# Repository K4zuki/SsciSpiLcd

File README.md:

# idea

- breadboard-able breakout board for color SPI memory LCD from Switch Science
    - https://www.switch-science.com/catalog/2858/

# spec

26.02x27.82 mm<sup>2</sup> LCD
- 42x35mm pcb
    - 4~6 panelize
- AkiSpiLcd compatible and extention
    - 541 buffer + 3-state buffer + NAND
- 23K256 SRAM
    - persudo DMA
- 3.3V LDO
- 1x8 pin headers left and right
    - VDD = 5V
    - GND
    - SPI.SCK
    - SPI.MOSI
    - SPI.MISO
    - SPI.CSL
    - SPI.CSR
    - LCD.DISP

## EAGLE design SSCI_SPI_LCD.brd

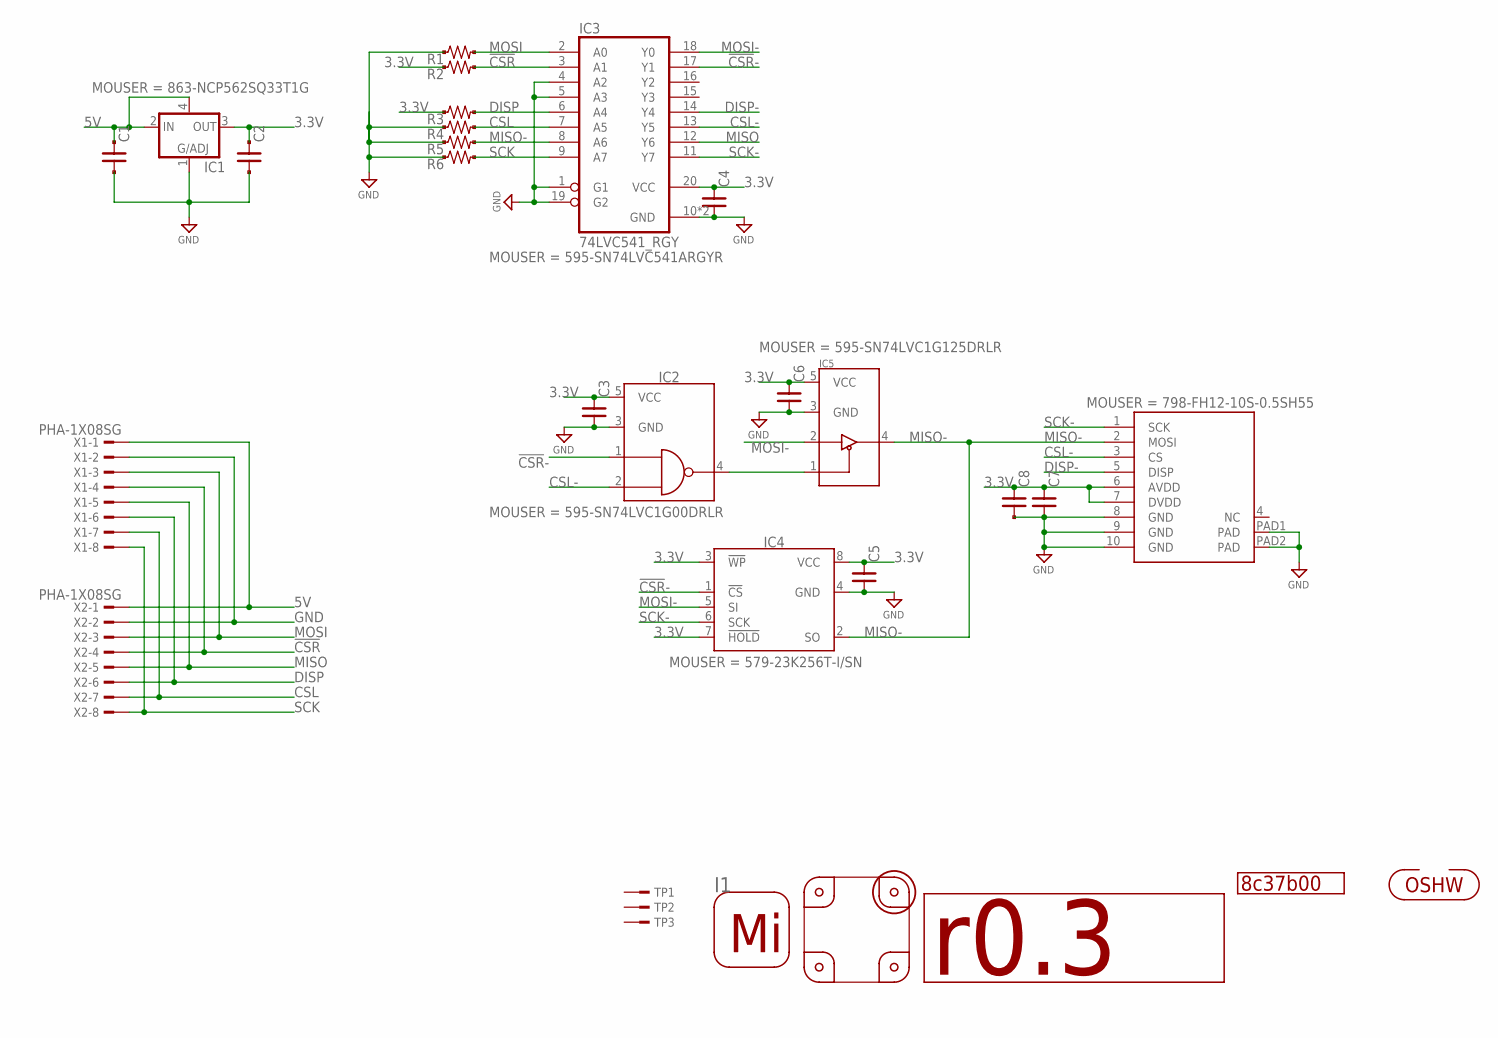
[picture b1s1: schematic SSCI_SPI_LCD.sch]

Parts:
C1, C2: C_SMD_10U_1608; CR_1608
C3, C4, C5, C6, C7, C8: C_SMD_0.1U_1005; C0402
GIT1: 8c37b00; GIT-REVISION_1.2
I1: ICON_MINLAB_5.2S; ICON_MINLAB_5.2MM
IC1: LDO4_3.3_SC82-AB; SOT130P220X135-4N
IC2: 74LVC1G00_DRL; SOT50P160X120-5N
IC3: 74LVC541_RGY; QFN50P460X360-20N
IC4: IC_MEMORY_8P_23K256-I_SOP; IC_08_1.27_150MIL
IC5: 74LVC1G125_DRL; SOT50P160X120-5N
ICON1: r0.3; ICON_REVISION1.7
ICON2: ICON_OSHW
LCD1: LCD_GLCD_400X240
P1, P2, P3, P4: PCB_CORNER_NH
R1, R2, R3, R4, R5, R6: R_US_10K_1005; C0402
TP1, TP2, TP3: TESTPAD_F; FIDUCIAL
X1, X2: PHA-1X08SG

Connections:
3.3V: C2.1, C3.1, C4.1, C5.1, C6.1, C7.1, C8.1, IC1.3 (OUT), IC2.5 (VCC), IC3.20 (VCC), IC4.3 (!WP), IC4.7 (!HOLD), IC4.8 (VCC), IC5.5 (VCC), LCD1.6 (AVDD), LCD1.7 (DVDD), R2.1, R3.1
5V: C1.1, IC1.2 (IN), IC1.4 (OUT/EN/NC), X1.1, X2.1
!CSR!: IC3.3 (A1), R2.2, X1.4, X2.4
!CSR!-: IC2.1 (1A), IC3.17 (Y1), IC4.1 (!CS)
CSL: IC3.7 (A5), R4.2, X1.7, X2.7
CSL-: IC2.2 (1B), IC3.13 (Y5), LCD1.3 (CS)
DISP: IC3.6 (A4), R3.2, X1.6, X2.6
DISP-: IC3.14 (Y4), LCD1.5 (DISP)
GND: C1.2, C2.2, C3.2, C4.2, C5.2, C6.2, C7.2, C8.2, IC1.1 (ADJ), IC2.3 (GND), IC3.1 (G1), IC3.4 (A2), IC3.5 (A3), IC3.10 (GND), IC3.19 (G2), IC3.EP (GND), IC4.4 (GND), IC5.3 (GND), LCD1.8 (GND), LCD1.9 (GND), LCD1.10 (GND), LCD1.PAD1 (PAD), LCD1.PAD2 (PAD), R1.1, R4.1, R5.1, R6.1, X1.2, X2.2
MISO: IC3.12 (Y6), X1.5, X2.5
MISO-: IC3.8 (A6), IC4.2 (SO), IC5.4 (Y), LCD1.2 (MOSI), R5.2
MOSI: IC3.2 (A0), R1.2, X1.3, X2.3
MOSI-: IC3.18 (Y0), IC4.5 (SI), IC5.2 (A)
unnamed: IC2.4 (1Y), IC5.1 (!OE!)
SCK: IC3.9 (A7), R6.2, X1.8, X2.8
SCK-: IC3.11 (Y7), IC4.6 (SCK), LCD1.1 (SCK)

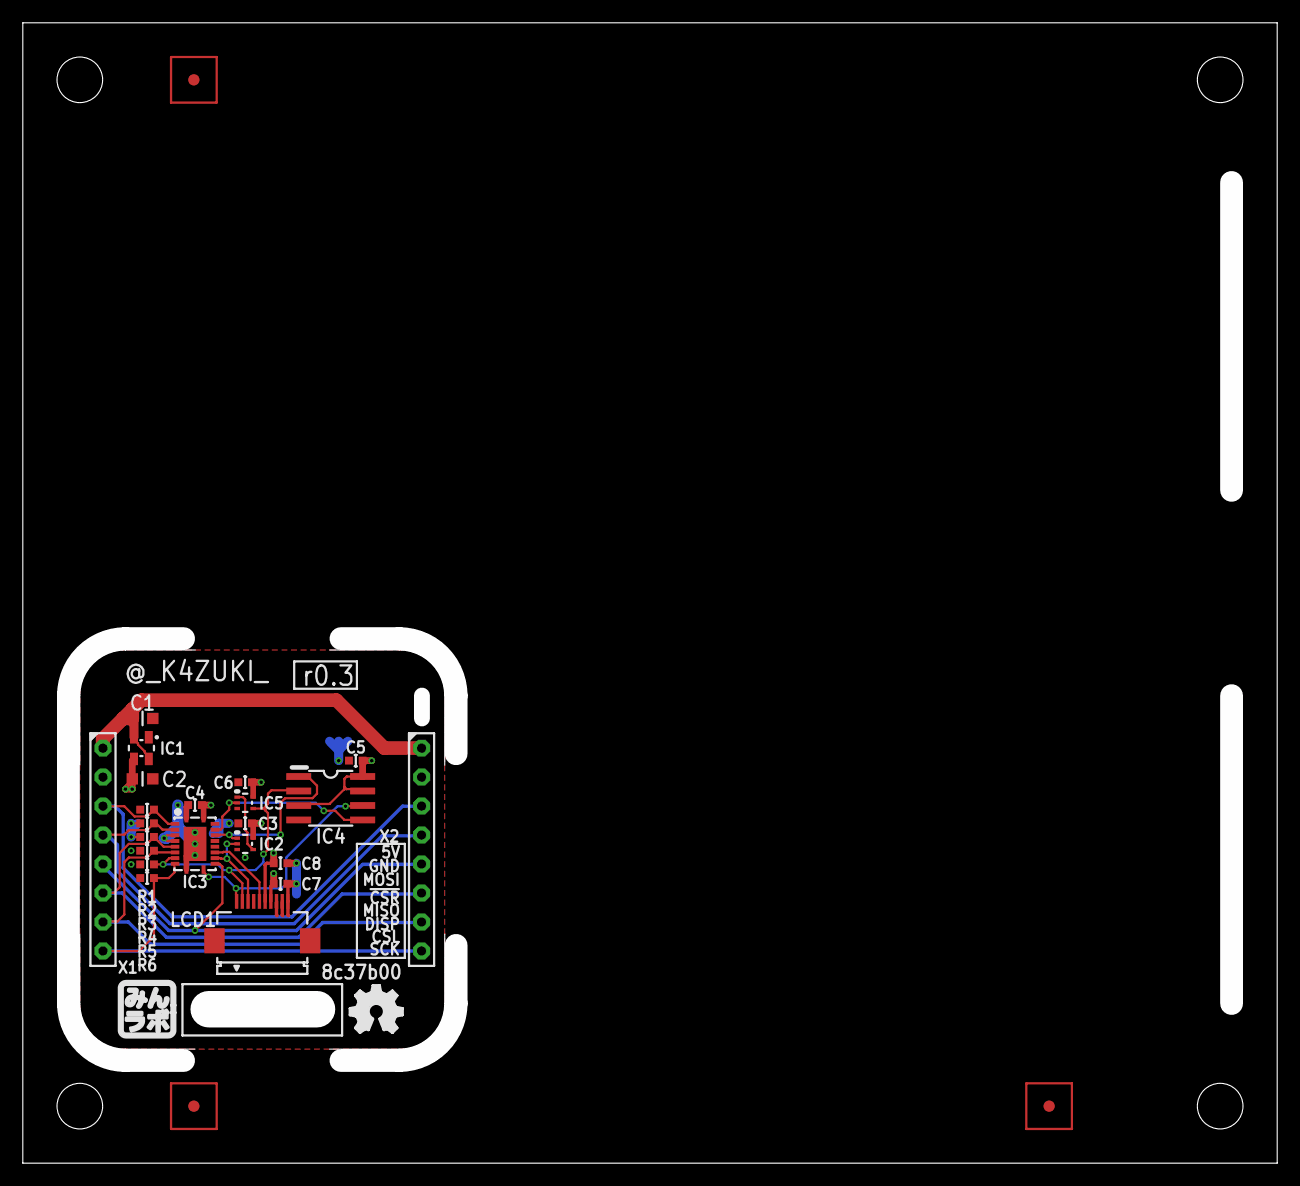
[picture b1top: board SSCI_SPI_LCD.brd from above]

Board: 2 copper layers, 106.8 x 96.8 mm, 33 parts (0 on the bottom side), 16 nets.

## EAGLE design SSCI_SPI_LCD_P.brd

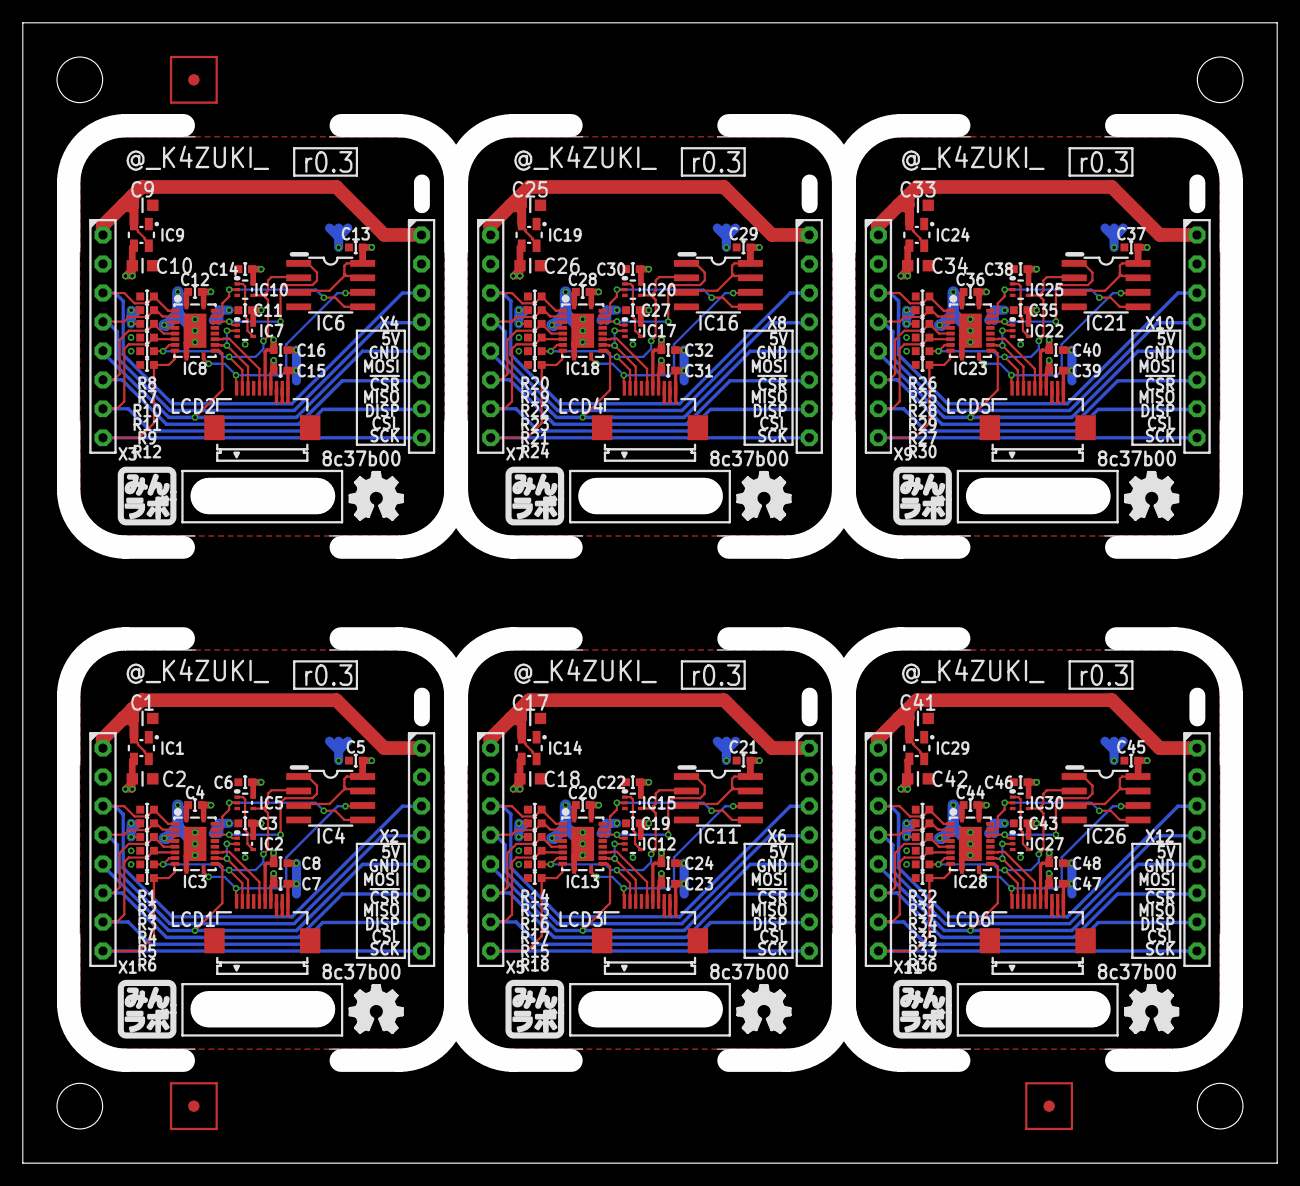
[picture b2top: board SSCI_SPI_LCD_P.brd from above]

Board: 2 copper layers, 106.8 x 96.8 mm, 183 parts (0 on the bottom side), 96 nets.

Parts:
C1, C2, C9, C10, C17, C18, C25, C26, C33, C34, C41, C42: CR_1608
C3, C4, C5, C6, C7, C8, C11, C12, C13, C14, C15, C16, C19, C20, C21, C22, C23, C24, C27, C28, C29, C30, C31, C32, C35, C36, C37, C38, C39, C40, C43, C44, C45, C46, C47, C48: C0402
GIT1, GIT2, GIT3, GIT4, GIT5, GIT6: 8c37b00; GIT-REVISION_1.2
I1, I2, I3, I4, I5, I6: ICON_MINLAB_5.2MM
IC1, IC9, IC14, IC19, IC24, IC29: SOT130P220X135-4N
IC2, IC5, IC7, IC10, IC12, IC15, IC17, IC20, IC22, IC25, IC27, IC30: SOT50P160X120-5N
IC3, IC8, IC13, IC18, IC23, IC28: 74LVC541_RGY; QFN50P460X360-20N
IC4, IC6, IC11, IC16, IC21, IC26: IC_08_1.27_150MIL
ICON1, ICON3, ICON5, ICON7, ICON9, ICON11: r0.3; ICON_REVISION1.7
ICON2, ICON4, ICON6, ICON8, ICON10, ICON12: ICON_OSHW
LCD1, LCD2, LCD3, LCD4, LCD5, LCD6: LCD_GLCD_400X240
P1, P2, P3, P4, P5, P6, P7, P8, P9, P10, P11, P12, P13, P14, P15, P16, P17, P18, P19, P20, P21, P22, P23, P24: PCB_CORNER_NH
R1, R2, R3, R4, R5, R6, R7, R8, R9, R10, R11, R12, R13, R14, R15, R16, R17, R18, R19, R20, R21, R22, R23, R24, R25, R26, R27, R28, R29, R30, R31, R32, R33, R34, R35, R36: C0402
TP1, TP2, TP3: FIDUCIAL
X1, X2, X3, X4, X5, X6, X7, X8, X9, X10, X11, X12: PHA-1X08SG

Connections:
3.3V: C2.1, C3.1, C4.1, C5.1, C6.1, C7.1, C8.1, IC1.3, IC2.5, IC3.20, IC4.3, IC4.7, IC4.8, IC5.5, LCD1.6, LCD1.7, R2.1, R3.1
3.3V1: C10.1, C11.1, C12.1, C13.1, C14.1, C15.1, C16.1, IC6.3, IC6.7, IC6.8, IC7.5, IC8.20, IC9.3, IC10.5, LCD2.6, LCD2.7, R7.1, R10.1
3.3V2: C18.1, C19.1, C20.1, C21.1, C22.1, C23.1, C24.1, IC11.3, IC11.7, IC11.8, IC12.5, IC13.20, IC14.3, IC15.5, LCD3.6, LCD3.7, R13.1, R16.1
3.3V3: C26.1, C27.1, C28.1, C29.1, C30.1, C31.1, C32.1, IC16.3, IC16.7, IC16.8, IC17.5, IC18.20, IC19.3, IC20.5, LCD4.6, LCD4.7, R19.1, R22.1
3.3V4: C34.1, C35.1, C36.1, C37.1, C38.1, C39.1, C40.1, IC21.3, IC21.7, IC21.8, IC22.5, IC23.20, IC24.3, IC25.5, LCD5.6, LCD5.7, R25.1, R28.1
3.3V5: C42.1, C43.1, C44.1, C45.1, C46.1, C47.1, C48.1, IC26.3, IC26.7, IC26.8, IC27.5, IC28.20, IC29.3, IC30.5, LCD6.6, LCD6.7, R31.1, R34.1
5V: C1.1, IC1.2, IC1.4, X1.1, X2.1
5V1: C9.1, IC9.2, IC9.4, X3.1, X4.1
5V2: C17.1, IC14.2, IC14.4, X5.1, X6.1
5V3: C25.1, IC19.2, IC19.4, X7.1, X8.1
5V4: C33.1, IC24.2, IC24.4, X9.1, X10.1
5V5: C41.1, IC29.2, IC29.4, X11.1, X12.1
!CSR!: IC3.3, R2.2, X1.4, X2.4
!CSR!1: IC8.3, R7.2, X3.4, X4.4
!CSR!2: IC13.3, R13.2, X5.4, X6.4
!CSR!3: IC18.3, R19.2, X7.4, X8.4
!CSR!4: IC23.3, R25.2, X9.4, X10.4
!CSR!5: IC28.3, R31.2, X11.4, X12.4
!CSR!-: IC2.1, IC3.17, IC4.1
!CSR!-1: IC6.1, IC7.1, IC8.17
!CSR!-2: IC11.1, IC12.1, IC13.17
!CSR!-3: IC16.1, IC17.1, IC18.17
!CSR!-4: IC21.1, IC22.1, IC23.17
!CSR!-5: IC26.1, IC27.1, IC28.17
CSL: IC3.7, R4.2, X1.7, X2.7
CSL1: IC8.7, R11.2, X3.7, X4.7
CSL2: IC13.7, R17.2, X5.7, X6.7
CSL3: IC18.7, R23.2, X7.7, X8.7
CSL4: IC23.7, R29.2, X9.7, X10.7
CSL5: IC28.7, R35.2, X11.7, X12.7
CSL-: IC2.2, IC3.13, LCD1.3
CSL-1: IC7.2, IC8.13, LCD2.3
CSL-2: IC12.2, IC13.13, LCD3.3
CSL-3: IC17.2, IC18.13, LCD4.3
CSL-4: IC22.2, IC23.13, LCD5.3
CSL-5: IC27.2, IC28.13, LCD6.3
DISP: IC3.6, R3.2, X1.6, X2.6
DISP1: IC8.6, R10.2, X3.6, X4.6
DISP2: IC13.6, R16.2, X5.6, X6.6
DISP3: IC18.6, R22.2, X7.6, X8.6
DISP4: IC23.6, R28.2, X9.6, X10.6
DISP5: IC28.6, R34.2, X11.6, X12.6
DISP-: IC3.14, LCD1.5
DISP-1: IC8.14, LCD2.5
DISP-2: IC13.14, LCD3.5
DISP-3: IC18.14, LCD4.5
DISP-4: IC23.14, LCD5.5
DISP-5: IC28.14, LCD6.5
GND: C1.2, C2.2, C3.2, C4.2, C5.2, C6.2, C7.2, C8.2, IC1.1, IC2.3, IC3.1, IC3.4, IC3.5, IC3.10, IC3.19, IC3.EP, IC4.4, IC5.3, LCD1.8, LCD1.9, LCD1.10, LCD1.PAD1, LCD1.PAD2, R1.1, R4.1, R5.1, R6.1, X1.2, X2.2
GND1: C9.2, C10.2, C11.2, C12.2, C13.2, C14.2, C15.2, C16.2, IC6.4, IC7.3, IC8.1, IC8.4, IC8.5, IC8.10, IC8.19, IC8.EP, IC9.1, IC10.3, LCD2.8, LCD2.9, LCD2.10, LCD2.PAD1, LCD2.PAD2, R8.1, R9.1, R11.1, R12.1, X3.2, X4.2
GND2: C17.2, C18.2, C19.2, C20.2, C21.2, C22.2, C23.2, C24.2, IC11.4, IC12.3, IC13.1, IC13.4, IC13.5, IC13.10, IC13.19, IC13.EP, IC14.1, IC15.3, LCD3.8, LCD3.9, LCD3.10, LCD3.PAD1, LCD3.PAD2, R14.1, R15.1, R17.1, R18.1, X5.2, X6.2
GND3: C25.2, C26.2, C27.2, C28.2, C29.2, C30.2, C31.2, C32.2, IC16.4, IC17.3, IC18.1, IC18.4, IC18.5, IC18.10, IC18.19, IC18.EP, IC19.1, IC20.3, LCD4.8, LCD4.9, LCD4.10, LCD4.PAD1, LCD4.PAD2, R20.1, R21.1, R23.1, R24.1, X7.2, X8.2
GND4: C33.2, C34.2, C35.2, C36.2, C37.2, C38.2, C39.2, C40.2, IC21.4, IC22.3, IC23.1, IC23.4, IC23.5, IC23.10, IC23.19, IC23.EP, IC24.1, IC25.3, LCD5.8, LCD5.9, LCD5.10, LCD5.PAD1, LCD5.PAD2, R26.1, R27.1, R29.1, R30.1, X9.2, X10.2
GND5: C41.2, C42.2, C43.2, C44.2, C45.2, C46.2, C47.2, C48.2, IC26.4, IC27.3, IC28.1, IC28.4, IC28.5, IC28.10, IC28.19, IC28.EP, IC29.1, IC30.3, LCD6.8, LCD6.9, LCD6.10, LCD6.PAD1, LCD6.PAD2, R32.1, R33.1, R35.1, R36.1, X11.2, X12.2
MISO: IC3.12, X1.5, X2.5
MISO1: IC8.12, X3.5, X4.5
MISO2: IC13.12, X5.5, X6.5
MISO3: IC18.12, X7.5, X8.5
MISO4: IC23.12, X9.5, X10.5
MISO5: IC28.12, X11.5, X12.5
MISO-: IC3.8, IC4.2, IC5.4, LCD1.2, R5.2
MISO-1: IC6.2, IC8.8, IC10.4, LCD2.2, R9.2
MISO-2: IC11.2, IC13.8, IC15.4, LCD3.2, R15.2
MISO-3: IC16.2, IC18.8, IC20.4, LCD4.2, R21.2
MISO-4: IC21.2, IC23.8, IC25.4, LCD5.2, R27.2
MISO-5: IC26.2, IC28.8, IC30.4, LCD6.2, R33.2
MOSI: IC3.2, R1.2, X1.3, X2.3
MOSI1: IC8.2, R8.2, X3.3, X4.3
MOSI2: IC13.2, R14.2, X5.3, X6.3
MOSI3: IC18.2, R20.2, X7.3, X8.3
MOSI4: IC23.2, R26.2, X9.3, X10.3
MOSI5: IC28.2, R32.2, X11.3, X12.3
MOSI-: IC3.18, IC4.5, IC5.2
MOSI-1: IC6.5, IC8.18, IC10.2
MOSI-2: IC11.5, IC13.18, IC15.2
MOSI-3: IC16.5, IC18.18, IC20.2
MOSI-4: IC21.5, IC23.18, IC25.2
MOSI-5: IC26.5, IC28.18, IC30.2
unnamed: IC7.4, IC10.1
unnamed: IC2.4, IC5.1
unnamed: IC12.4, IC15.1
unnamed: IC17.4, IC20.1
unnamed: IC22.4, IC25.1
unnamed: IC27.4, IC30.1
SCK: IC3.9, R6.2, X1.8, X2.8
SCK1: IC8.9, R12.2, X3.8, X4.8
SCK2: IC13.9, R18.2, X5.8, X6.8
SCK3: IC18.9, R24.2, X7.8, X8.8
SCK4: IC23.9, R30.2, X9.8, X10.8
SCK5: IC28.9, R36.2, X11.8, X12.8
SCK-: IC3.11, IC4.6, LCD1.1
SCK-1: IC6.6, IC8.11, LCD2.1
SCK-2: IC11.6, IC13.11, LCD3.1
SCK-3: IC16.6, IC18.11, LCD4.1
SCK-4: IC21.6, IC23.11, LCD5.1
SCK-5: IC26.6, IC28.11, LCD6.1

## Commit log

2016-10-11 add sch/brd files
2016-10-11 r0.1 prototype
2016-10-11 connectors silk
2016-10-12 rename gist to README.md
2016-10-12 revision 0.1
2016-10-12 remove binary from repo
2016-10-12 not Dimension but tRestrict/bRestrict to cut copper pour
2016-10-19 better routing; library update
2016-10-22 Board size get narrower by 2mm; related moves; library updates
    Board size:
    42x35mm -> 40x35mm
    Moves:
    - X1/2 connectors
    - CR and ICs
    - Version/Revision/Names silk
2016-10-24 apply changes to panelising file
2016-11-14 add MinLab icon; moves
2016-11-14 update libraries; update panelise; update gerbers
2017-01-03 [ BRD ] add fiducial
2017-01-03 [ BRD ] replace pinheader; revision 0.3; add corner 4.0mm holes
2017-01-03 [ BRD ] add C5 ground via; git revision update
2017-01-03 [ BRD ] add measures
    - hole to hole
    - board edge to pin header center
2017-01-03 [ BRD ] add pin silk on bottom
2017-01-03 [ BRD ] X1/X2 silk moved
2017-01-03 [ BRD ] panelized
2017-01-03 gerber out with bottom silk
2017-01-03 ignore *.log
2017-01-07 update markdowns
2017-01-07 update git revision; remove unnecessary tRestrict
2017-01-27 pin header distance get 200mil narrower
    - 1300mil -> 1100mil
    - matches with "standard" breadboard
2017-07-26 update library
2017-07-26 outline resized
    - no more corner screw holes
    - still panelized in 110x100(3x2)
2017-07-26 R3 connected to 3.3V (to pull up DISP pin)
    - left-top corner(at LCD top view) has key-hole
2017-07-30 keyhole replaced by milling
    X2 note is tPlace layer
2017-07-30 8c37b00 panelized
2017-07-30 r0.3 gerber updated
